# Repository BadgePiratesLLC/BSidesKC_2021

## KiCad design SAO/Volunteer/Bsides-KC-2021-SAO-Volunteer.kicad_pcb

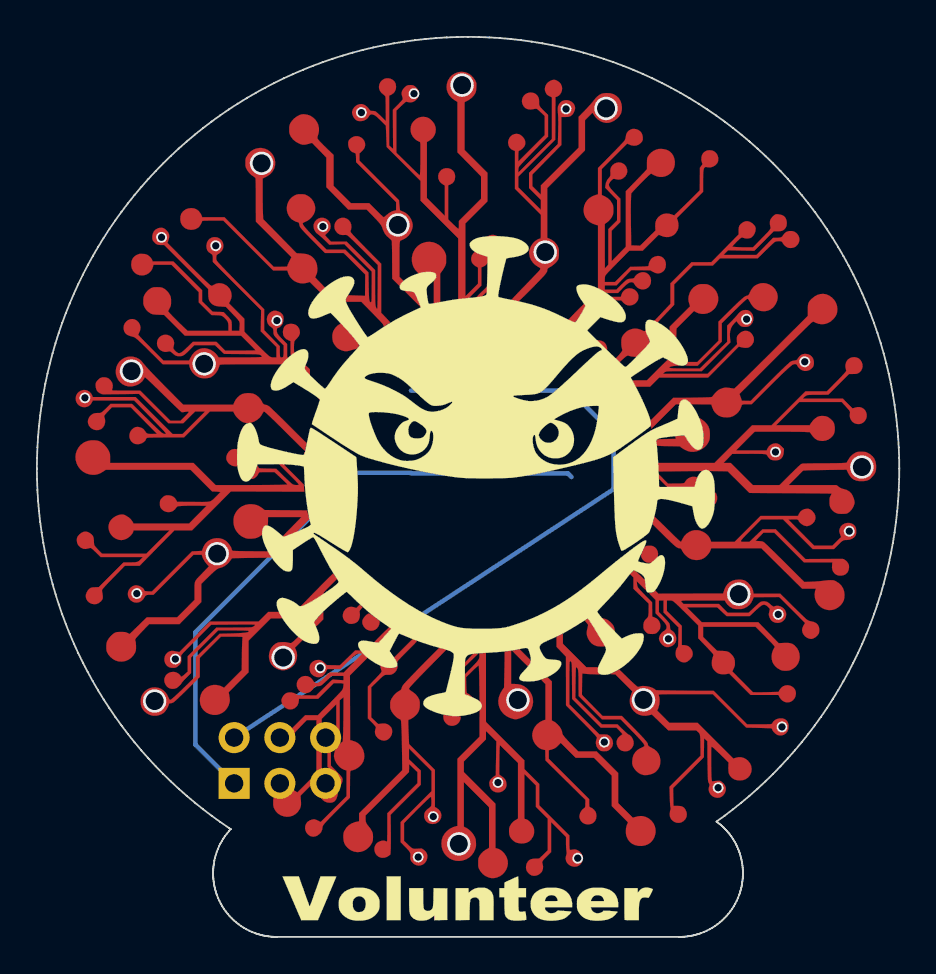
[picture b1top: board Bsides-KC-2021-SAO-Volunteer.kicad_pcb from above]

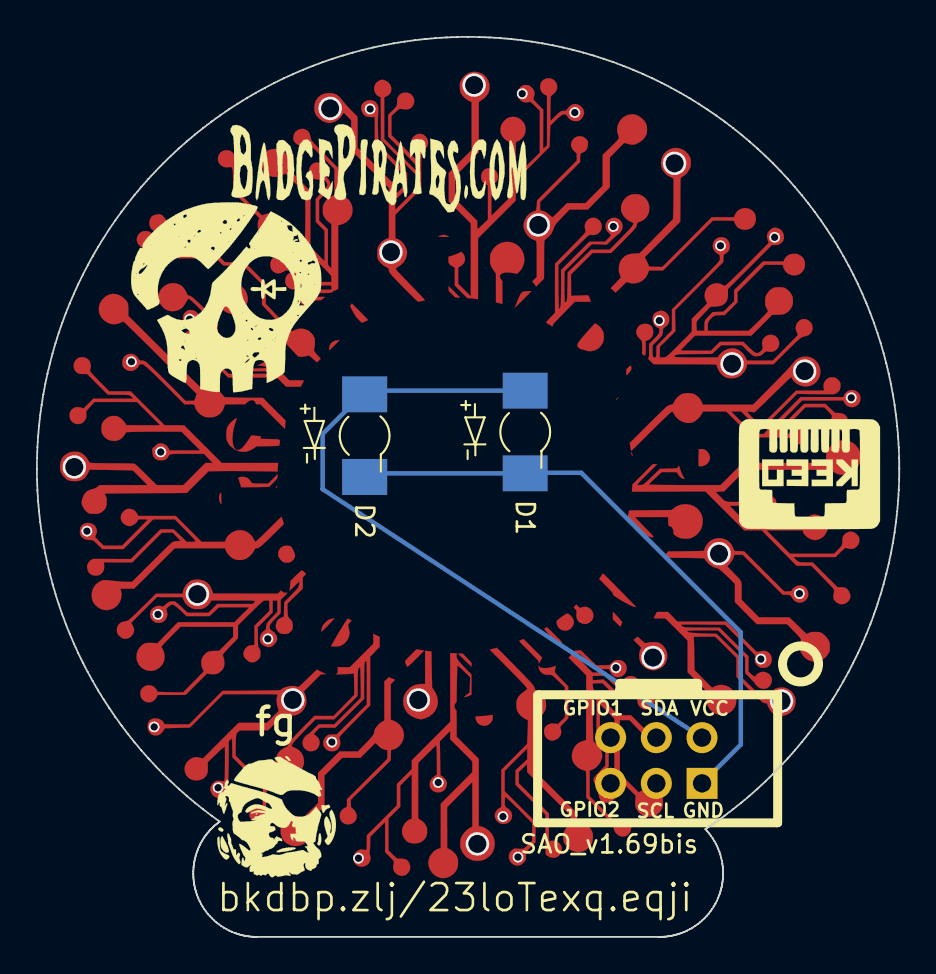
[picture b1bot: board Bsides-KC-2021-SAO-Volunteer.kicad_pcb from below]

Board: 2 copper layers, 47.9 x 50.0 mm, 3 parts (2 on the bottom side), 2 nets.

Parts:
D1, D2: LED; LED_Osram_Lx_P47F_D2mm_ReverseMount_MaskNoHole
X1: SAO_v1.69bis; Badgelife-SAOv169-BADGE-2x3_Back

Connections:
GND: D1.1, D2.1, X1.2
VCC: D1.2, D2.2, X1.1

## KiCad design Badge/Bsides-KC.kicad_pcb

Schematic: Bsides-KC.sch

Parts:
BT1: Battery_Cell; BatteryHolder_MPD_BC2003_1x2032
J1: Conn_01x02_Male; PinHeader_1x02_P2.54mm_Vertical
SW1: SW_SPDT; SW_SPDT_CK-JS102011SAQN
X1, X2, X3, X4, X5, X6, X7, X8, X9, X10, X11, X12: Badgelife_sao_connector_v169bis; Badgelife-SAOv169-BADGE-2x3_Back

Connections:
GND: BT1.2 (-), J1.2, X1.2, X2.2, X3.2, X4.2, X5.2, X6.2, X7.2, X8.2, X9.2, X10.2, X11.2, X12.2
unnamed: BT1.1 (+), SW1.2 (B)
VCC: J1.1, SW1.3 (C), X1.1, X2.1, X3.1, X4.1, X5.1, X6.1, X7.1, X8.1, X9.1, X10.1, X11.1, X12.1

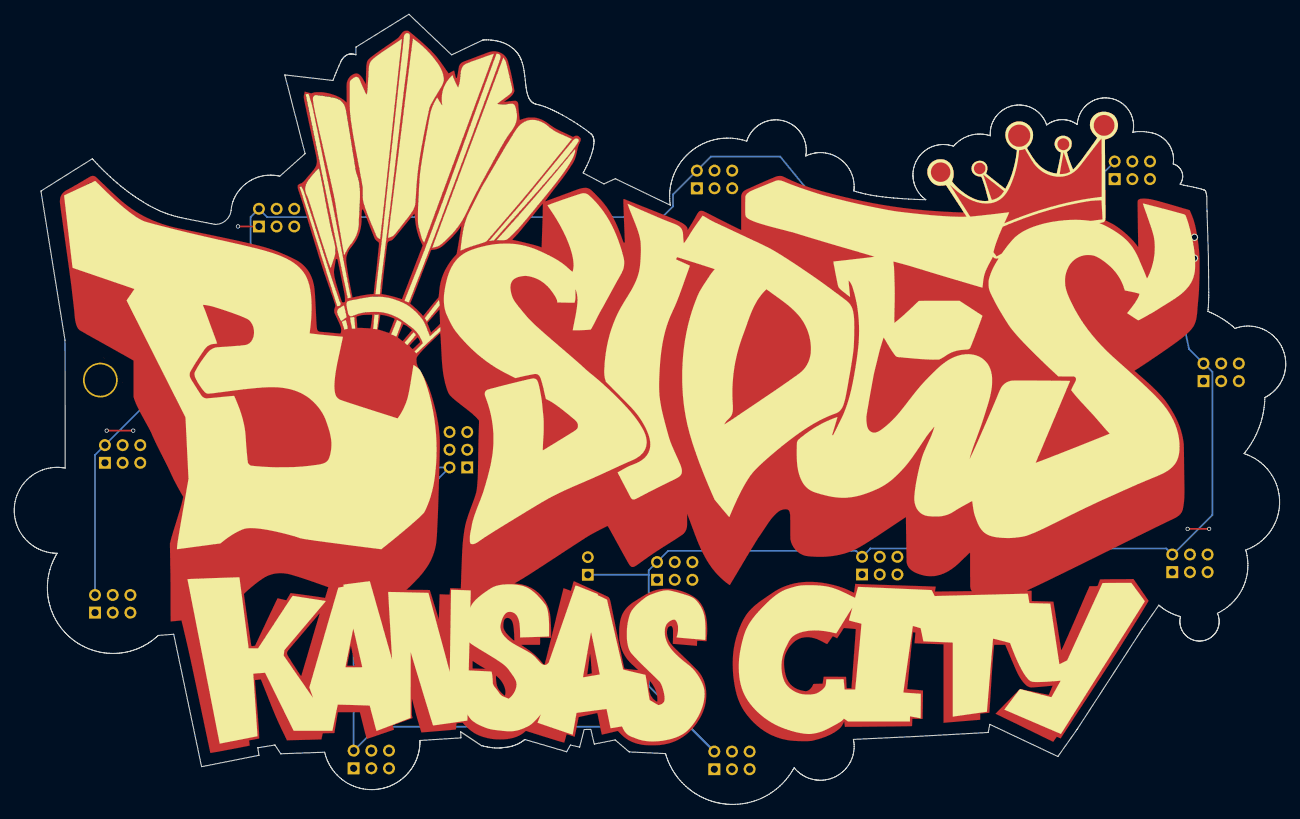
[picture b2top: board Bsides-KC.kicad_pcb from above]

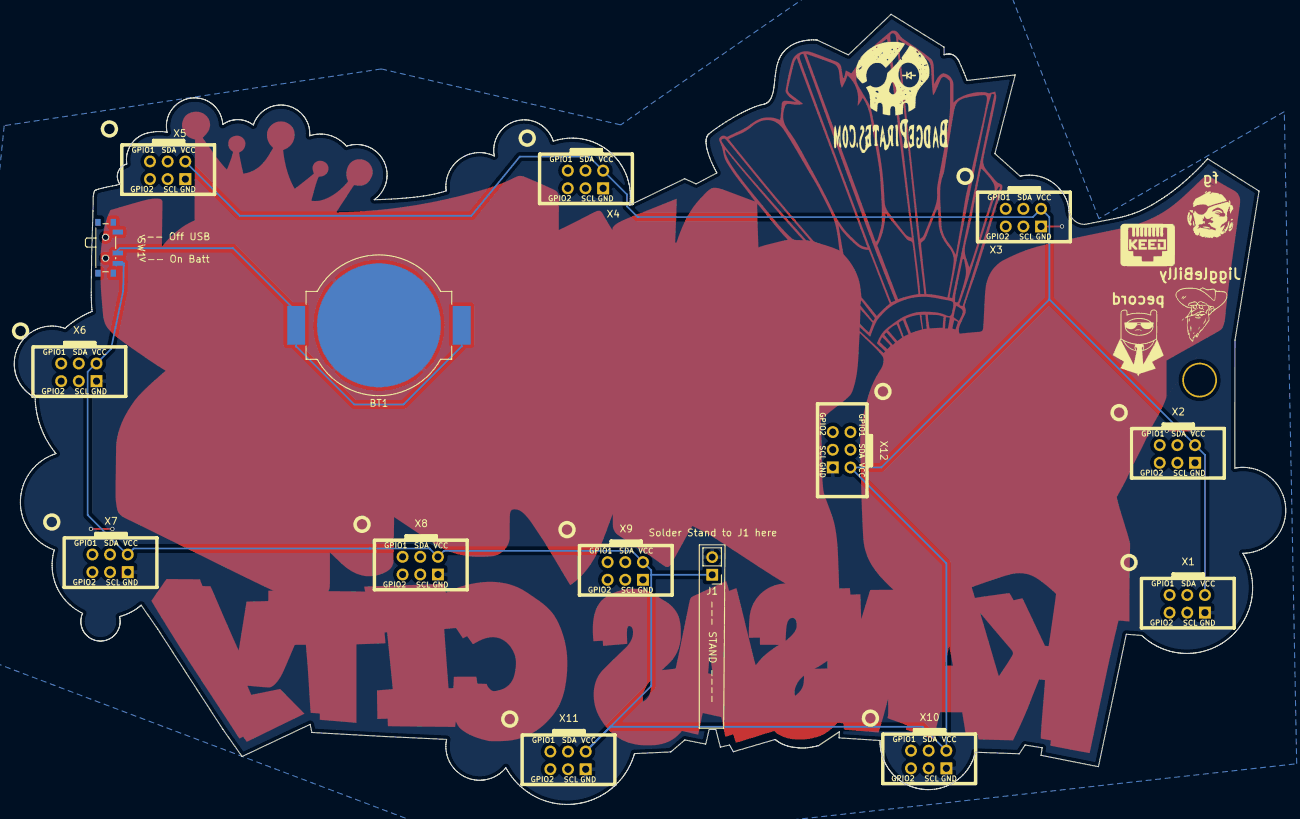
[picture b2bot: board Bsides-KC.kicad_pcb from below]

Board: 2 copper layers, 182.7 x 113.6 mm, 15 parts (3 on the bottom side), 3 nets.

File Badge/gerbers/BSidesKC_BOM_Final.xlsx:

Id | Designator | Package | Quantity | Designation | Supplier and ref | Column1 | _1
1 | SW1 | SW_SPDT_PCM12 | 1 | SW_SPDT | SK-32965-01-L1
2 | G*** | Jiggle_10x15_BSILK | 1 | JiggleBilly |  | DNP
3 | G*** | NG_BSilk | 1 | NG_BSilk |  | DNP
4 | G*** | FG_10x10_BSILK | 1 | fg |  | DNP
5 | G*** | BadgePiratesURL_BSLK | 1 | LOGO |  | DNP
6 | G*** | BPSkull_Distressed_10x10_BSILK | 1 | BP Logo |  | DNP
7 | G*** | pecord | 1 | pecord |  | DNP
8 | J1 | PinHeader_1x02_P2.54mm_Vertical | 1 | Conn_01x02_Male |  | DNP
9 | X2,X12,X11,X10,X9,X8,X7,X6,X5,X4,X3,X1 | Badgelife-SAOv169-BADGE-2x3_Back | 12 | Badgelife_sao_connector_v169bis |  | DNP
10 | REF** | Hole_4.5mm | 1 | 4.5mm |  | DNP
11 | BT1 | BatteryHolder_MPD_BC2003_1x2032 | 1 | Battery_Cell | BAT-HLD-001
12 | G***,G***,G***,G***,G***,G***,G*** | LOGO | 7 | LOGO |  | DNP

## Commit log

2021-09-27 Initial Push
2021-09-27 removing to clean first
2022-04-08 Added Badge Folder with all files
2022-04-08 Uploading SAO files
